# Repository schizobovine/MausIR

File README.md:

# MausIR
Making some toys for my cats.

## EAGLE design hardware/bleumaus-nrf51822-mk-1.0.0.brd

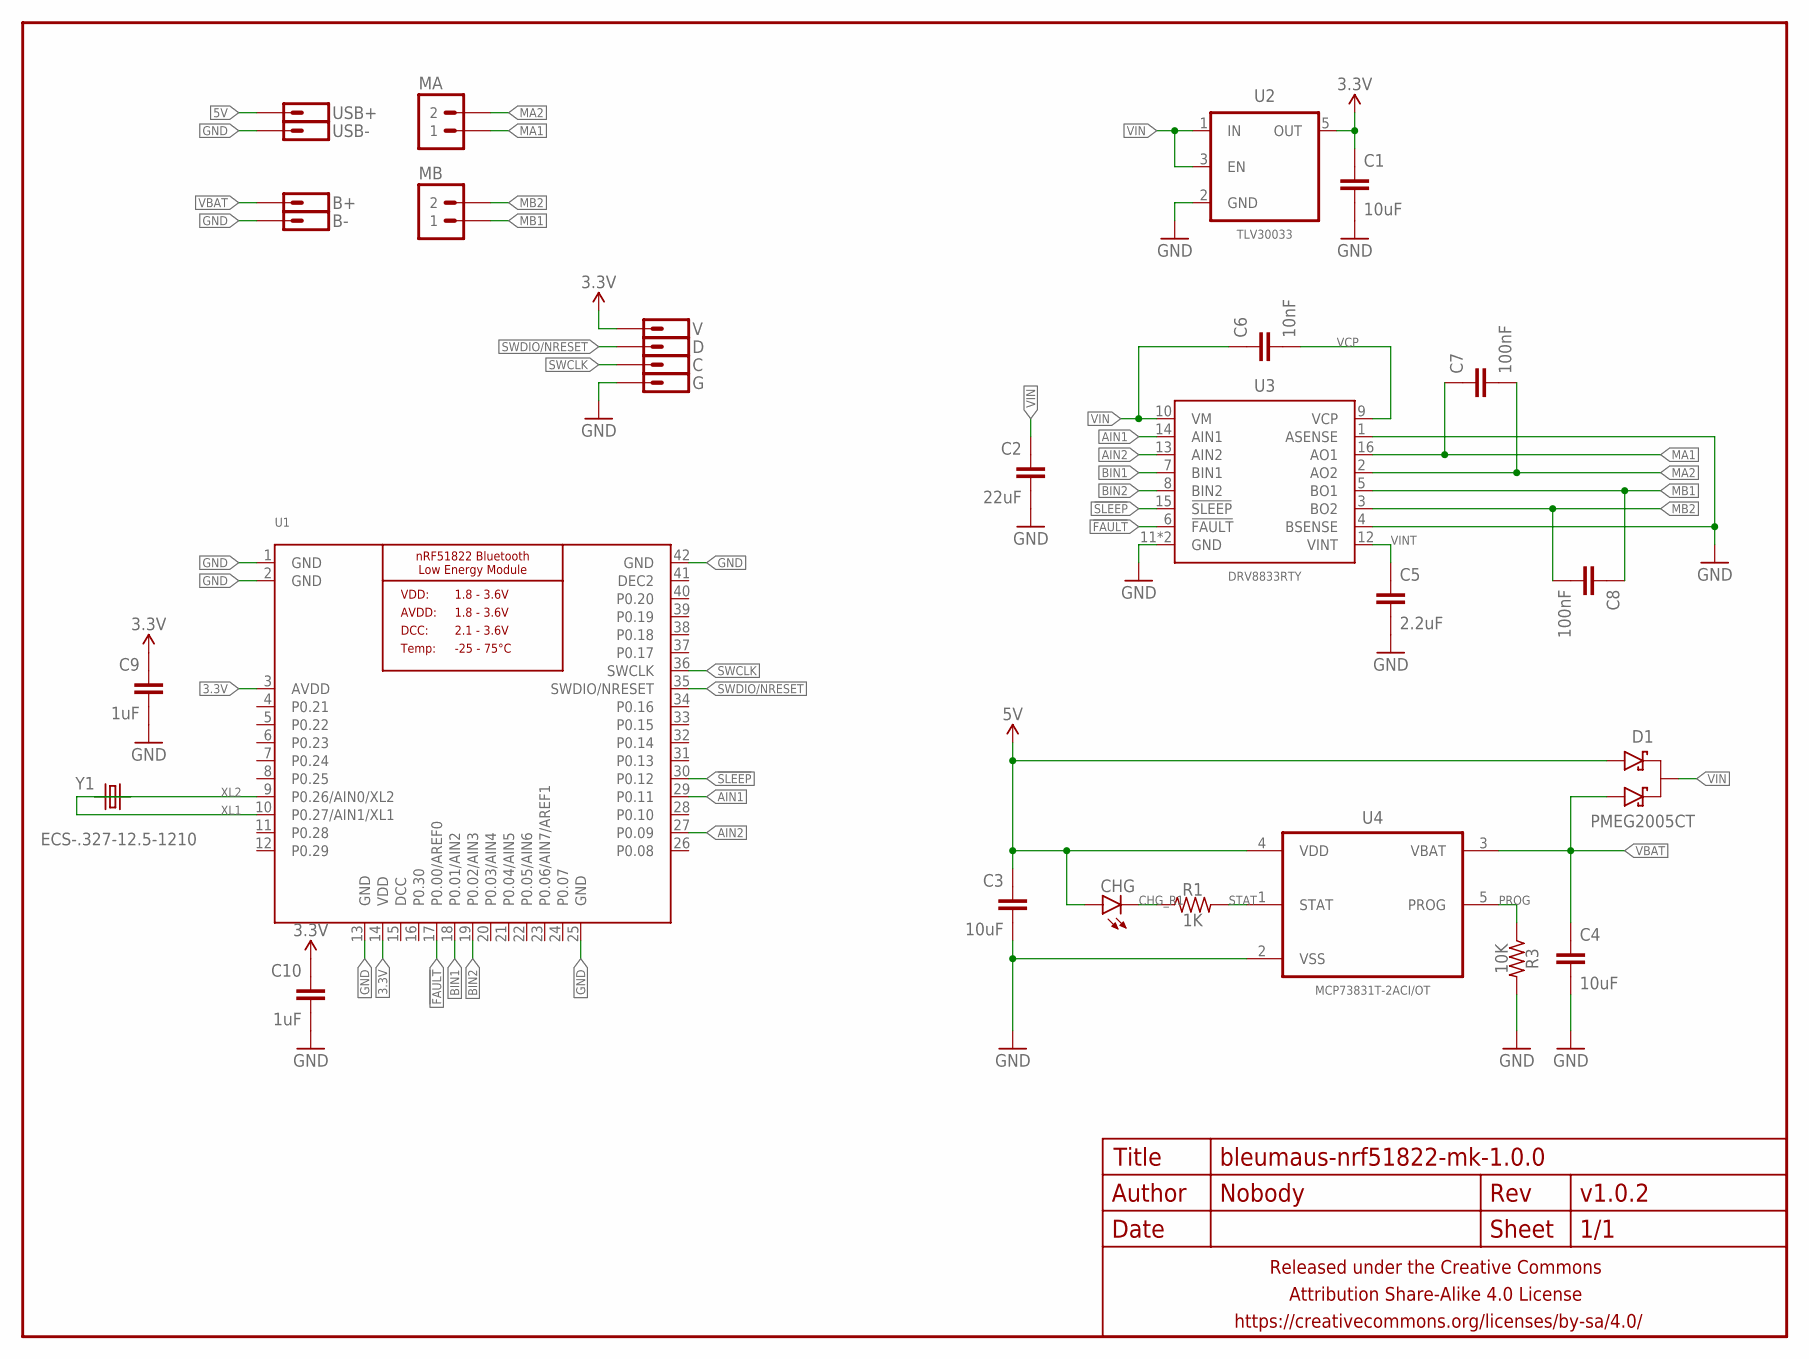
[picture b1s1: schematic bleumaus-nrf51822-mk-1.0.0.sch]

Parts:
B+: M01SMD-1DIA; 1X01-SMD-1MM-DIA
B-: M01SMD-1DIA; 1X01-SMD-1MM-DIA
C: M01SMD-1DIA; 1X01-SMD-1MM-DIA
C1, C3, C4: 10uF; C0402
C2: 22uF; C1206
C5: 2.2uF; C0402
C6: 10nF; C0402
C7, C8: 100nF; C0402
C9, C10: 1uF; C0402
CHG: LED0603-TIGHT; LED-0603-TIGHT
D: M01SMD-1DIA; 1X01-SMD-1MM-DIA
D1: PMEG2005CT; SOT23
FRAME1: FRAME-LETTERNO_PACKAGE; DUMMY
G: M01SMD-1DIA; 1X01-SMD-1MM-DIA
MA: M02PTH-2MM; 1X02-2MM-PTH
MB: M02PTH-2MM; 1X02-2MM-PTH
R1: 1K; R0402
R3: 10K; R0402
U1: NRF51822_MODULE_MDBT40; BLE_MODULE_RAYTAC_MDBT40
U2: TLV30033; SC70-TIGHTER
U3: DRV8833RTY; PWQFN-16
U4: MCP73831T-2ACI/OT; SOT95P280X145-5N
USB+: M01SMD-1DIA; 1X01-SMD-1MM-DIA
USB-: M01SMD-1DIA; 1X01-SMD-1MM-DIA
V: M01SMD-1DIA; 1X01-SMD-1MM-DIA
Y1: ECS-.327-12.5-1210; CRYSTAL-1X1.2MM

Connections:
3.3V: C1.1, C9.1, C10.1, U1.3 (AVDD), U1.14 (VDD), U2.5 (OUT), V.P$1
5V: C3.1, CHG.A, D1.1 (A1), U4.4 (VDD), USB+.P$1
!FAULT: U1.17 (P0.00/AREF0), U3.6 (!FAULT)
!SLEEP: U1.30 (P0.12), U3.15 (!SLEEP)
AIN1: U1.29 (P0.11), U3.14 (AIN1)
AIN2: U1.27 (P0.09), U3.13 (AIN2)
BIN1: U1.18 (P0.01/AIN2), U3.7 (BIN1)
BIN2: U1.19 (P0.02/AIN3), U3.8 (BIN2)
CHG_R1: CHG.C, R1.1
DCC: U1.15 (DCC)
DEC2: U1.41 (DEC2)
GND: B-.P$1, C1.2, C2.2, C3.2, C4.2, C5.2, C9.2, C10.2, G.P$1, R3.2, U1.1 (GND), U1.2 (GND), U1.13 (GND), U1.25 (GND), U1.42 (GND), U2.2 (GND), U3.1 (ASENSE), U3.4 (BSENSE), U3.11 (GND), U3.17 (GND), U4.2 (VSS), USB-.P$1
MA1: C7.1, MA.P$1 (1), U3.16 (AO1)
MA2: C7.2, MA.P$2 (2), U3.2 (AO2)
MB1: C8.1, MB.P$1 (1), U3.5 (BO1)
MB2: C8.2, MB.P$2 (2), U3.3 (BO2)
PROG: R3.1, U4.5 (PROG)
STAT: R1.2, U4.1 (STAT)
SWCLK: C.P$1, U1.36 (SWCLK)
SWDIO/NRESET: D.P$1, U1.35 (SWDIO/NRESET)
VBAT: B+.P$1, C4.1, D1.2 (A2), U4.3 (VBAT)
VCP: C6.2, U3.9 (VCP)
VIN: C2.1, C6.1, D1.3 (K), U2.1 (IN), U2.3 (EN), U3.10 (VM)
VINT: C5.1, U3.12 (VINT)
XL1: U1.10 (P0.27/AIN1/XL1), Y1.1
XL2: U1.9 (P0.26/AIN0/XL2), Y1.2

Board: 2 copper layers, 30 parts (19 on the bottom side), 24 nets, no tracks yet.

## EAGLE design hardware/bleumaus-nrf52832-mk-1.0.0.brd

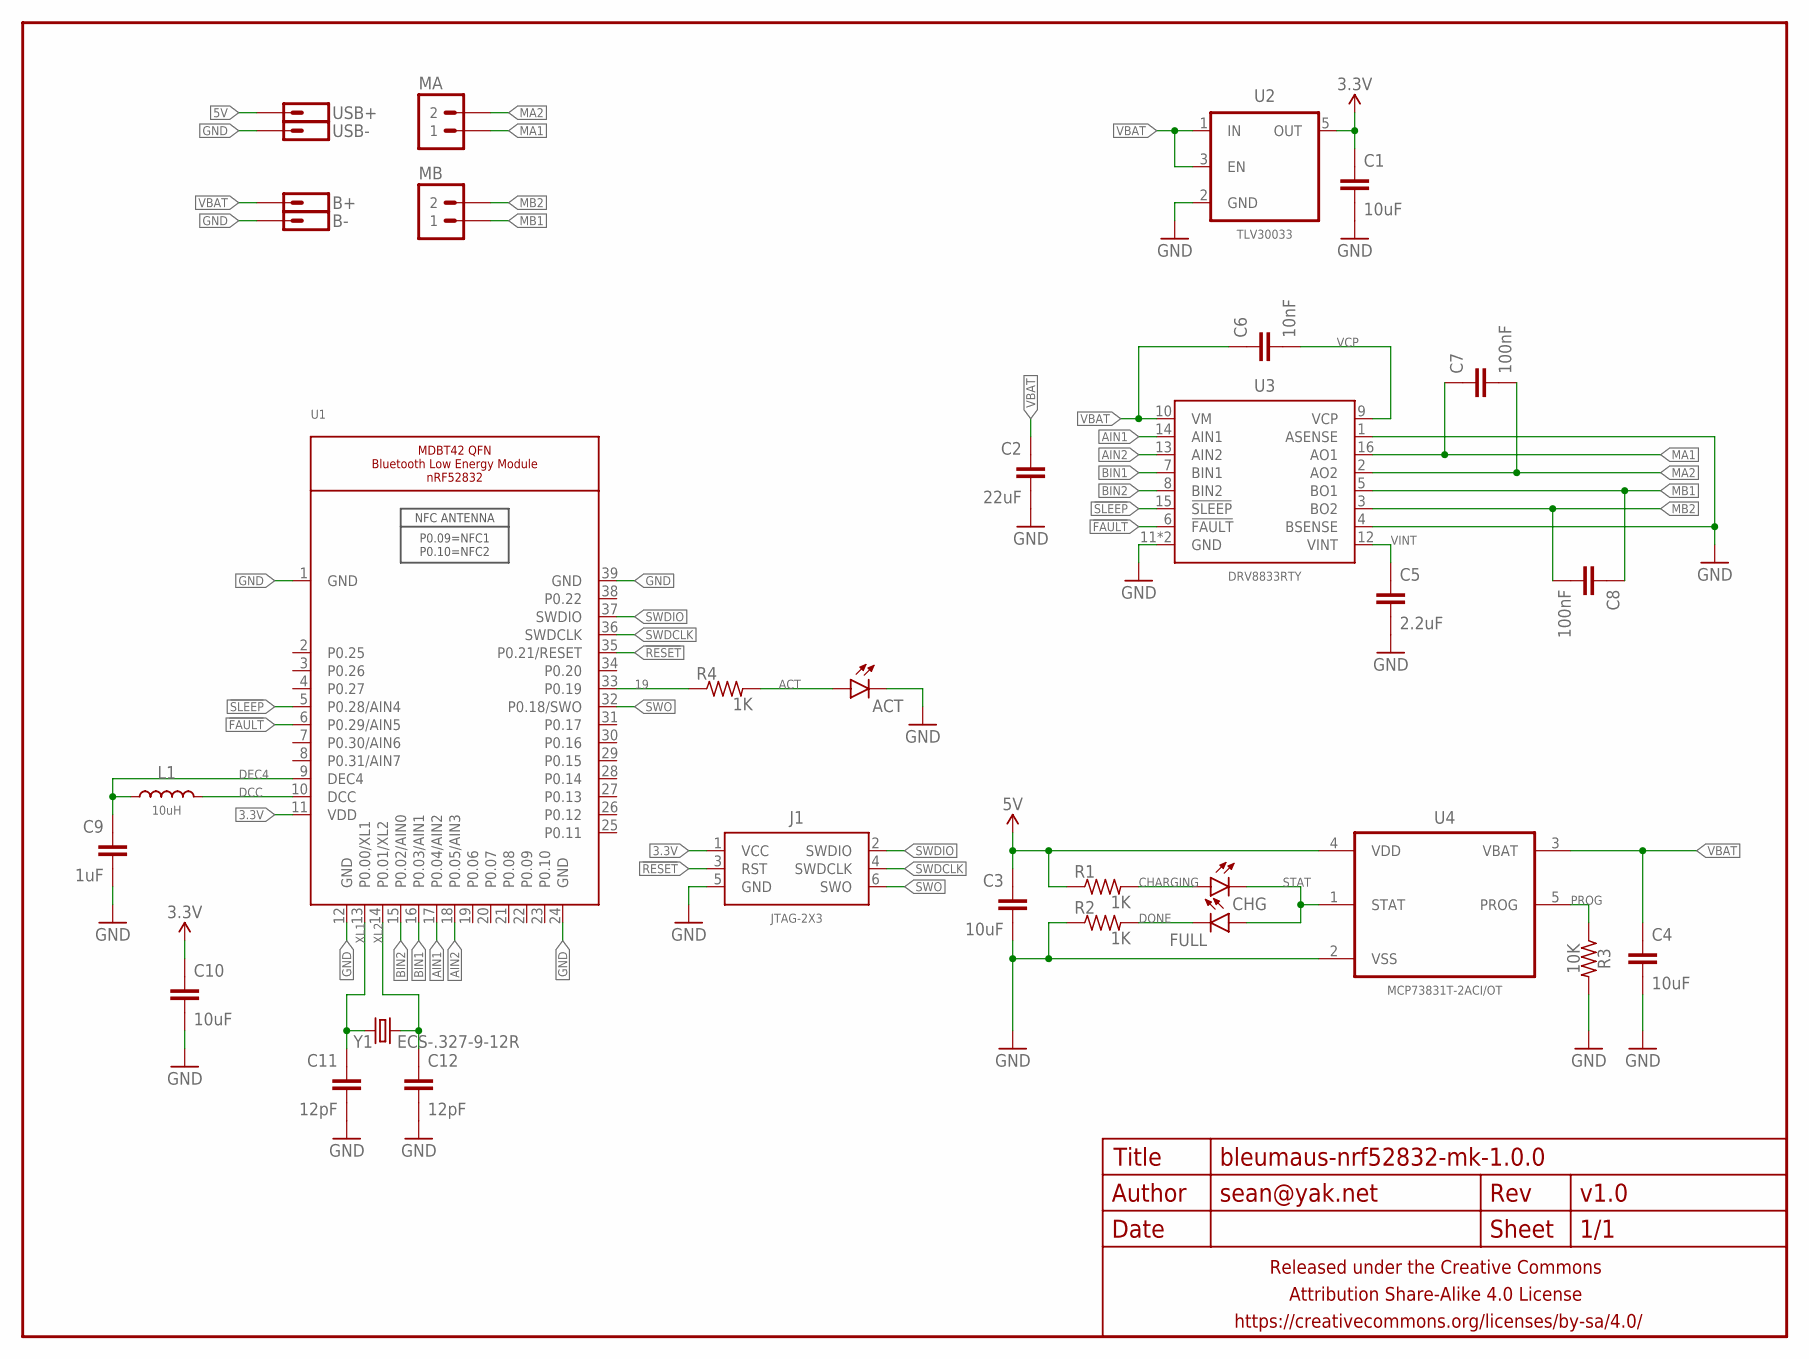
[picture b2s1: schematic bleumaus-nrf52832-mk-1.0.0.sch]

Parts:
ACT: LED0603-TIGHT; LED-0603-TIGHT
B+: M01SMD-1DIA; 1X01-SMD-1MM-DIA
B-: M01SMD-1DIA; 1X01-SMD-1MM-DIA
C1, C3, C4: 10uF; C0402
C2: 22uF; C1206
C5: 2.2uF; C0402
C6: 10nF; C0402
C7, C8: 100nF; C0402
C9: 1uF; C0402
C10: 10uF; C0603-TIGHTER
C11, C12: 12pF; C0402
CHG: LED0603-TIGHT; LED-0603-TIGHT
FRAME1: FRAME-LETTERNO_PACKAGE; DUMMY
FULL: LED0603-TIGHT; LED-0603-TIGHT
J1: JTAG-2X3; 2X3-1.27MM-SMD
L1: 10uH; 0603
MA: M02PTH-2MM; 1X02-2MM-PTH
MB: M02PTH-2MM; 1X02-2MM-PTH
R1, R2, R4: 1K; R0402
R3: 10K; R0402
U1: NRF52832_MODULE_MDBT42_NO2324; BLE_MODULE_RAYTAC_MDBT42_NO2324
U2: TLV30033; SC70-TIGHTER
U3: DRV8833RTY; PWQFN-16
U4: MCP73831T-2ACI/OT; SOT95P280X145-5N
USB+: M01SMD-1DIA; 1X01-SMD-1MM-DIA
USB-: M01SMD-1DIA; 1X01-SMD-1MM-DIA
Y1: ECS-.327-9-12R; CRYSTAL-2X1.2MM

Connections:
3.3V: C1.1, C10.1, J1.1 (VCC), U1.11 (VDD), U2.5 (OUT)
5V: C3.1, R1.1, U4.4 (VDD), USB+.P$1
19: R4.1, U1.33 (P0.19)
!FAULT: U1.6 (P0.29/AIN5), U3.6 (!FAULT)
!RESET: J1.3 (RST), U1.35 (P0.21/RESET)
!SLEEP: U1.5 (P0.28/AIN4), U3.15 (!SLEEP)
ACT: ACT.A, R4.2
AIN1: U1.17 (P0.04/AIN2), U3.14 (AIN1)
AIN2: U1.18 (P0.05/AIN3), U3.13 (AIN2)
BIN1: U1.16 (P0.03/AIN1), U3.7 (BIN1)
BIN2: U1.15 (P0.02/AIN0), U3.8 (BIN2)
CHARGING: CHG.A, R1.2
DCC: L1.2, U1.10 (DCC)
DEC4: C9.1, L1.1, U1.9 (DEC4)
DONE: FULL.C, R2.2
GND: ACT.C, B-.P$1, C1.2, C2.2, C3.2, C4.2, C5.2, C9.2, C10.2, C11.2, C12.2, J1.5 (GND), R2.1, R3.2, U1.1 (GND), U1.12 (GND), U1.24 (GND), U1.39 (GND), U2.2 (GND), U3.1 (ASENSE), U3.4 (BSENSE), U3.11 (GND), U3.17 (GND), U4.2 (VSS), USB-.P$1
MA1: C7.1, MA.P$1 (1), U3.16 (AO1)
MA2: C7.2, MA.P$2 (2), U3.2 (AO2)
MB1: C8.1, MB.P$1 (1), U3.5 (BO1)
MB2: C8.2, MB.P$2 (2), U3.3 (BO2)
PROG: R3.1, U4.5 (PROG)
STAT: CHG.C, FULL.A, U4.1 (STAT)
SWDCLK: J1.4 (SWDCLK), U1.36 (SWDCLK)
SWDIO: J1.2 (SWDIO), U1.37 (SWDIO)
SWO: J1.6 (SWO), U1.32 (P0.18/SWO)
VBAT: B+.P$1, C2.1, C4.1, C6.1, U2.1 (IN), U2.3 (EN), U3.10 (VM), U4.3 (VBAT)
VCP: C6.2, U3.9 (VCP)
VINT: C5.1, U3.12 (VINT)
XL1: C11.1, U1.13 (P0.00/XL1), Y1.1
XL2: C12.1, U1.14 (P0.01/XL2), Y1.2

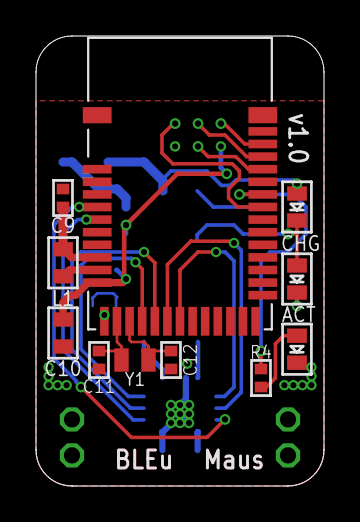
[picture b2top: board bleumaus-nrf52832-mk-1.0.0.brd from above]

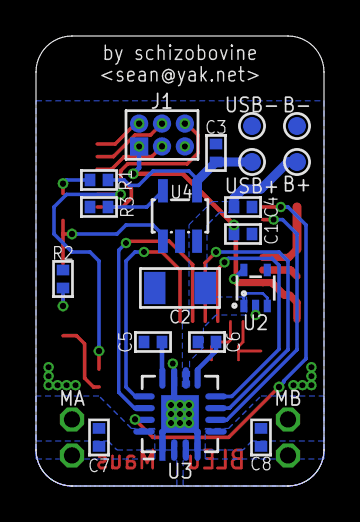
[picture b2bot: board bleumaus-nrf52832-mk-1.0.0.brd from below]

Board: 2 copper layers, 16.0 x 25.0 mm, 33 parts (21 on the bottom side), 30 nets.

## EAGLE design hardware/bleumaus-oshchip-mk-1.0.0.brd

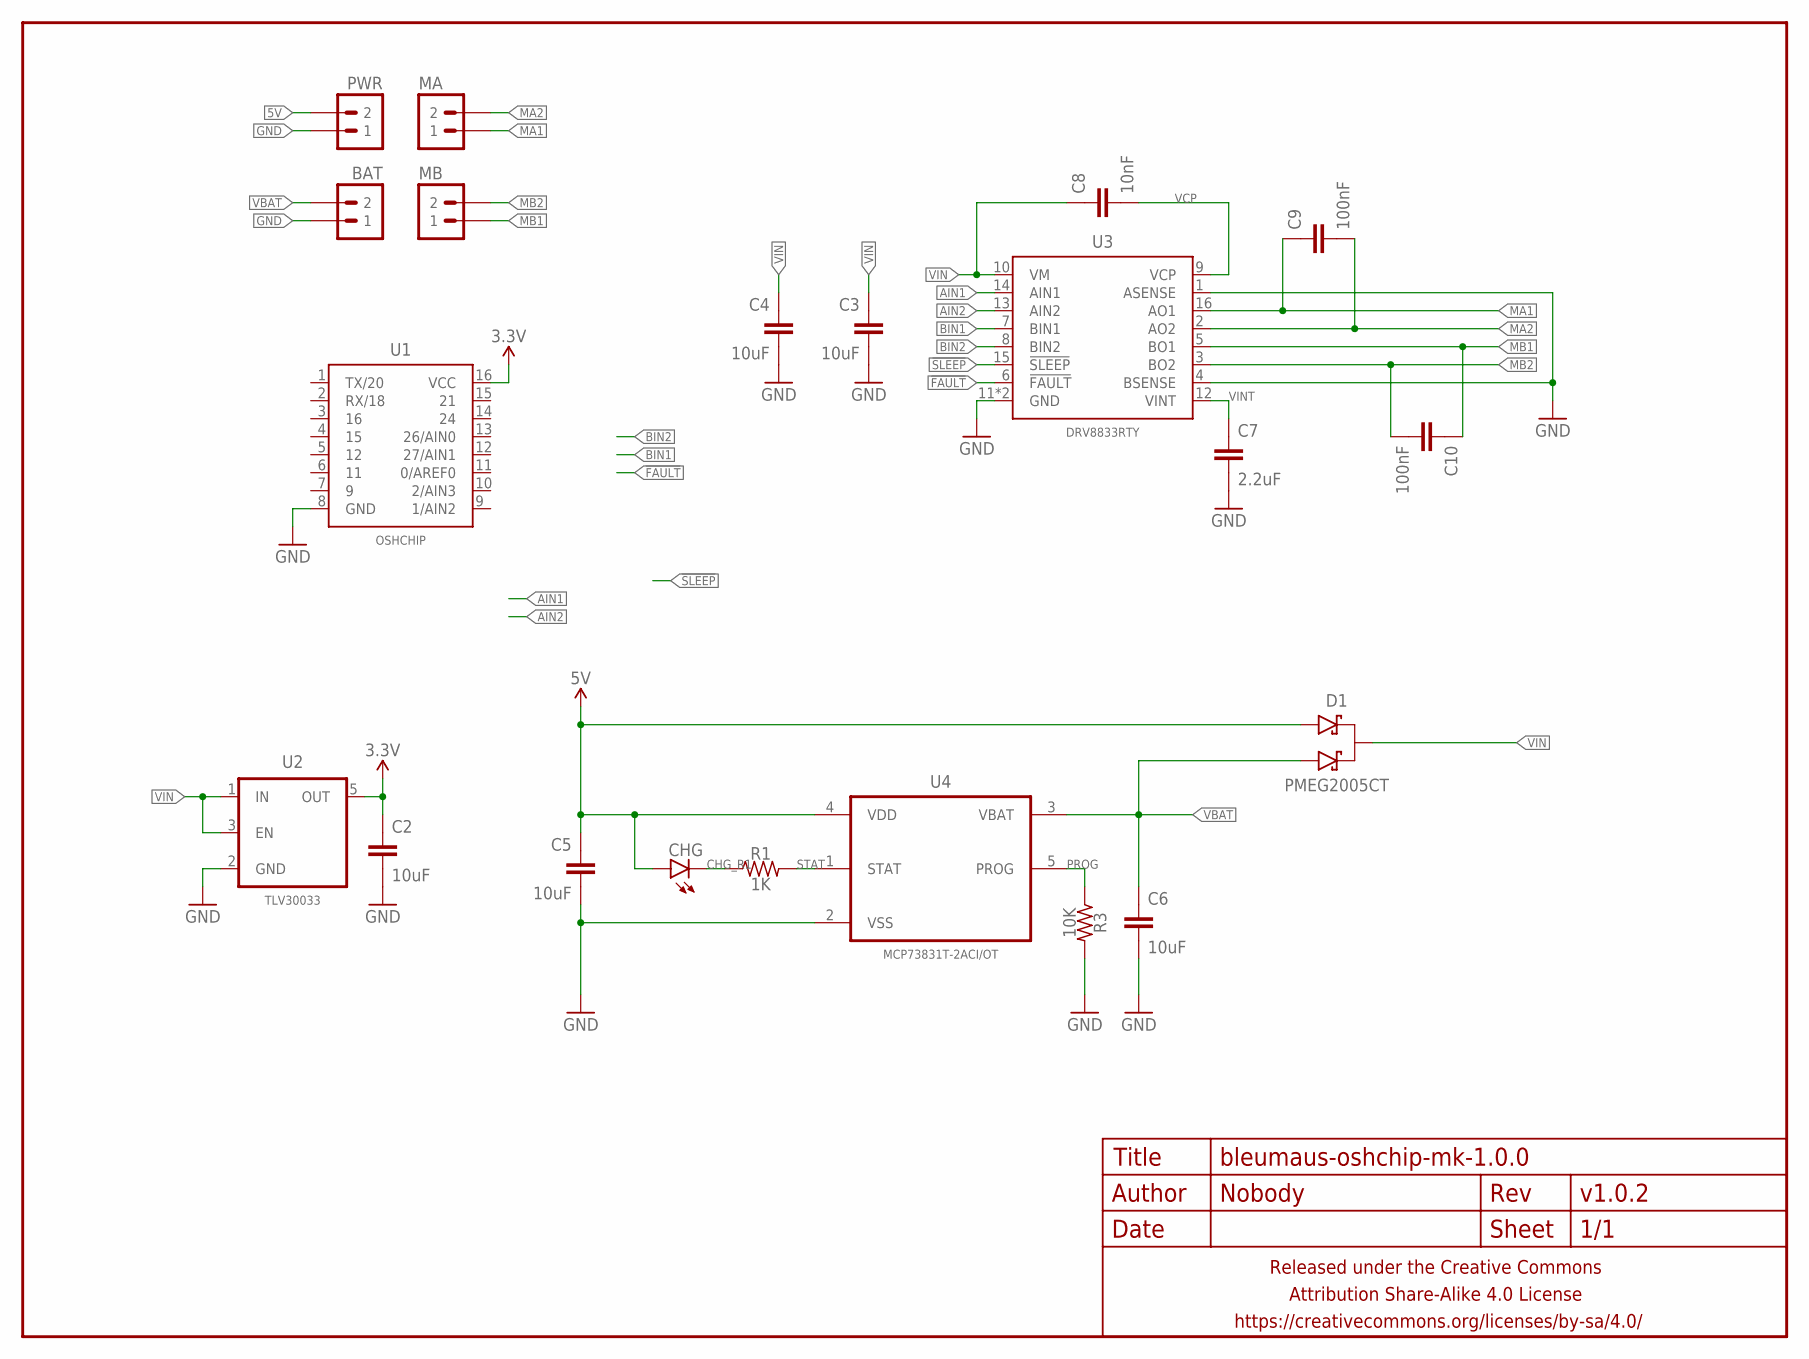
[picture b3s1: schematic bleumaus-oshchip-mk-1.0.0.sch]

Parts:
BAT: M02PTH-2MM; 1X02-2MM-PTH
C2, C5, C6: 10uF; C0402
C3, C4: 10uF; C1206
C7: 2.2uF; C0402
C8: 10nF; C0402
C9, C10: 100nF; C0402
CHG: LED0603-TIGHT; LED-0603-TIGHT
D1: PMEG2005CT; SOT23
FRAME1: FRAME-LETTERNO_PACKAGE; DUMMY
MA: M02PTH-2MM; 1X02-2MM-PTH
MB: M02PTH-2MM; 1X02-2MM-PTH
PWR: M02PTH-2MM; 1X02-2MM-PTH
R1: 1K; R0402
R3: 10K; R0402
U1: OSHCHIP; DIL16
U2: TLV30033; SC70-TIGHTER
U3: DRV8833RTY; PWQFN-16
U4: MCP73831T-2ACI/OT; SOT95P280X145-5N

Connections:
3.3V: C2.1, U1.16 (VCC), U2.5 (OUT)
5V: C5.1, CHG.A, D1.1 (A1), PWR.P$2 (2), U4.4 (VDD)
!FAULT: U3.6 (!FAULT)
!SLEEP: U3.15 (!SLEEP)
AIN1: U3.14 (AIN1)
AIN2: U3.13 (AIN2)
BIN1: U3.7 (BIN1)
BIN2: U3.8 (BIN2)
CHG_R1: CHG.C, R1.1
GND: BAT.P$1 (1), C2.2, C3.2, C4.2, C5.2, C6.2, C7.2, PWR.P$1 (1), R3.2, U1.8 (GND), U2.2 (GND), U3.1 (ASENSE), U3.4 (BSENSE), U3.11 (GND), U3.17 (GND), U4.2 (VSS)
MA1: C9.1, MA.P$1 (1), U3.16 (AO1)
MA2: C9.2, MA.P$2 (2), U3.2 (AO2)
MB1: C10.1, MB.P$1 (1), U3.5 (BO1)
MB2: C10.2, MB.P$2 (2), U3.3 (BO2)
PROG: R3.1, U4.5 (PROG)
STAT: R1.2, U4.1 (STAT)
VBAT: BAT.P$2 (2), C6.1, D1.2 (A2), U4.3 (VBAT)
VCP: C8.2, U3.9 (VCP)
VIN: C3.1, C4.1, C8.1, D1.3 (K), U2.1 (IN), U2.3 (EN), U3.10 (VM)
VINT: C7.1, U3.12 (VINT)

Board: 2 copper layers, 22 parts (2 on the bottom side), 14 nets, no tracks yet.

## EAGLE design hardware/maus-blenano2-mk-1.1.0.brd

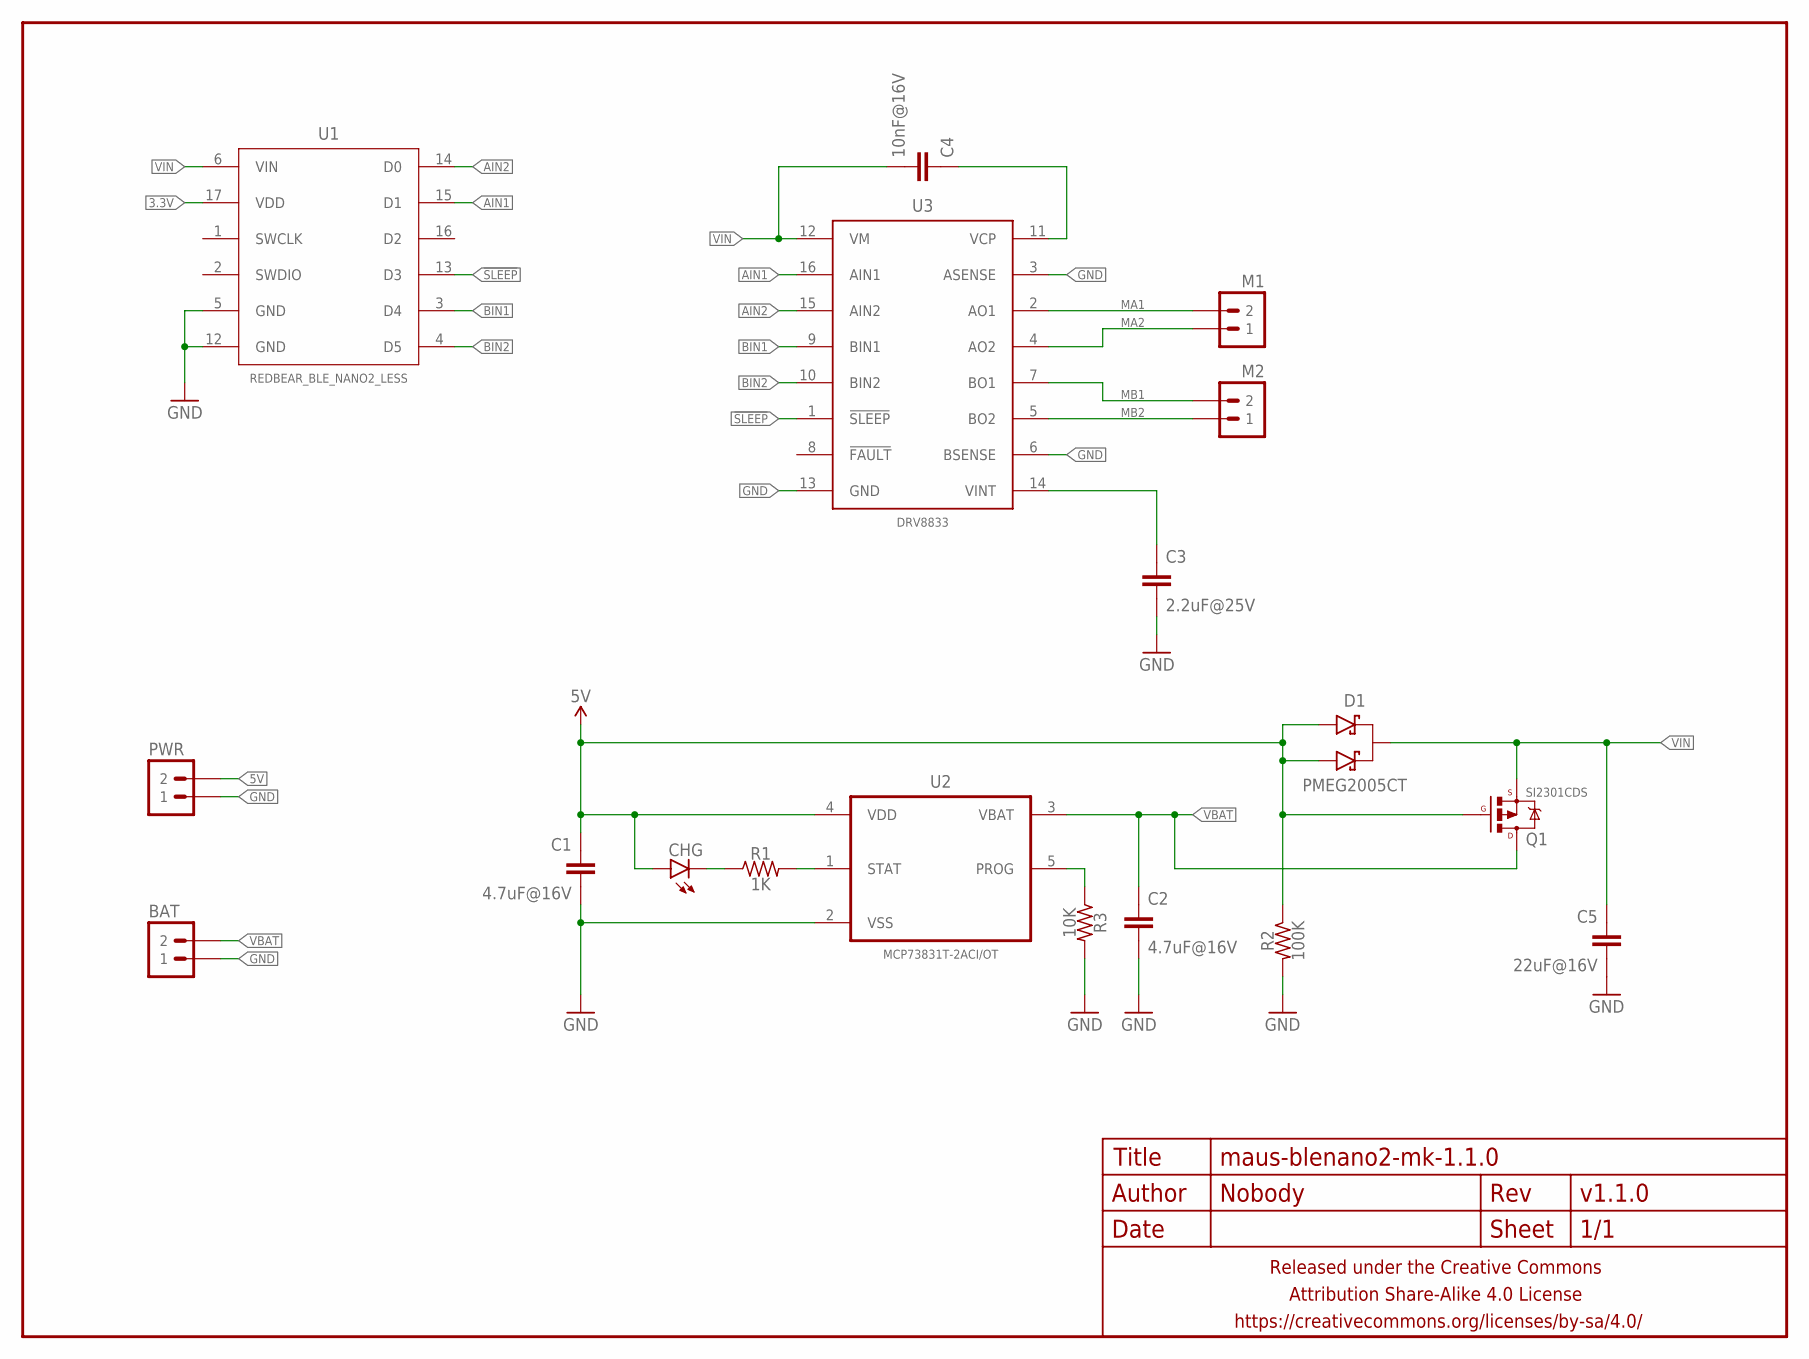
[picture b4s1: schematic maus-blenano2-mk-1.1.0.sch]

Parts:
BAT: M02PTH-2MM; 1X02-2MM-PTH
C1, C2: 4.7uF@16V; C0603-TIGHTER
C3: 2.2uF@25V; C0603
C4: 10nF@16V; C0402
C5: 22uF@16V; C1206
CHG: LED0603-TIGHT; LED-0603-TIGHT
D1: PMEG2005CT; SOT23
FRAME1: FRAME-LETTERNO_PACKAGE; DUMMY
M1, M2: M02PTH-2MM; 1X02-2MM-PTH
PWR: M02PTH-2MM; 1X02-2MM-PTH
Q1: SI2301CDS; SOT23
R1: 1K; R0603-TIGHTER
R2: 100K; R0603-TIGHTER
R3: 10K; R0603-TIGHTER
U1: REDBEAR_BLE_NANO2_LESS
U2: MCP73831T-2ACI/OT; SOT95P280X145-5N
U3: DRV8833; TSSOP16

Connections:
3.3V: U1.17 (VDD)
5V: C1.1, CHG.A, D1.1 (A1), D1.2 (A2), PWR.P$2 (2), Q1.1 (G), R2.1, U2.4 (VDD)
!SLEEP: U1.13 (D3), U3.1 (!SLEEP)
AIN1: U1.15 (D1), U3.16 (AIN1)
AIN2: U1.14 (D0), U3.15 (AIN2)
BIN1: U1.3 (D4), U3.9 (BIN1)
BIN2: U1.4 (D5), U3.10 (BIN2)
GND: BAT.P$1 (1), C1.2, C2.2, C3.2, C5.2, PWR.P$1 (1), R2.2, R3.2, U1.5 (GND), U1.12 (GND), U2.2 (VSS), U3.3 (ASENSE), U3.6 (BSENSE), U3.13 (GND)
MA1: M1.P$2 (2), U3.2 (AO1)
MA2: M1.P$1 (1), U3.4 (AO2)
MB1: M2.P$2 (2), U3.7 (BO1)
MB2: M2.P$1 (1), U3.5 (BO2)
unnamed: R1.2, U2.1 (STAT)
unnamed: CHG.C, R1.1
unnamed: C3.1, U3.14 (VINT)
unnamed: C4.1, U3.11 (VCP)
unnamed: R3.1, U2.5 (PROG)
VBAT: BAT.P$2 (2), C2.1, Q1.3 (D), U2.3 (VBAT)
VIN: C4.2, C5.1, D1.3 (K), Q1.2 (S), U1.6 (VIN), U3.12 (VM)

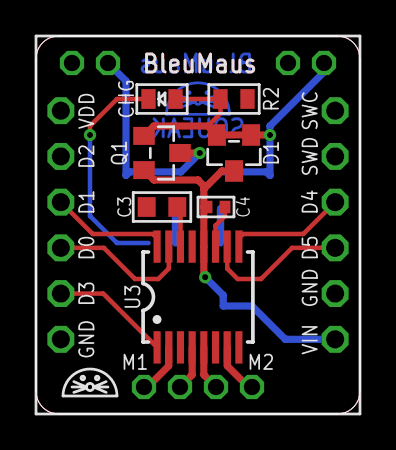
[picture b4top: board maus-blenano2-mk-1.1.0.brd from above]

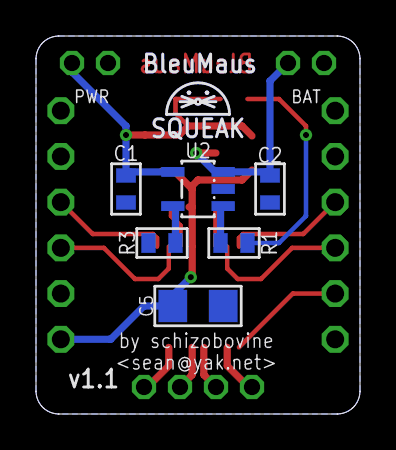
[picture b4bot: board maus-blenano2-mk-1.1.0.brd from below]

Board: 2 copper layers, 18.0 x 21.0 mm, 19 parts (8 on the bottom side), 18 nets.

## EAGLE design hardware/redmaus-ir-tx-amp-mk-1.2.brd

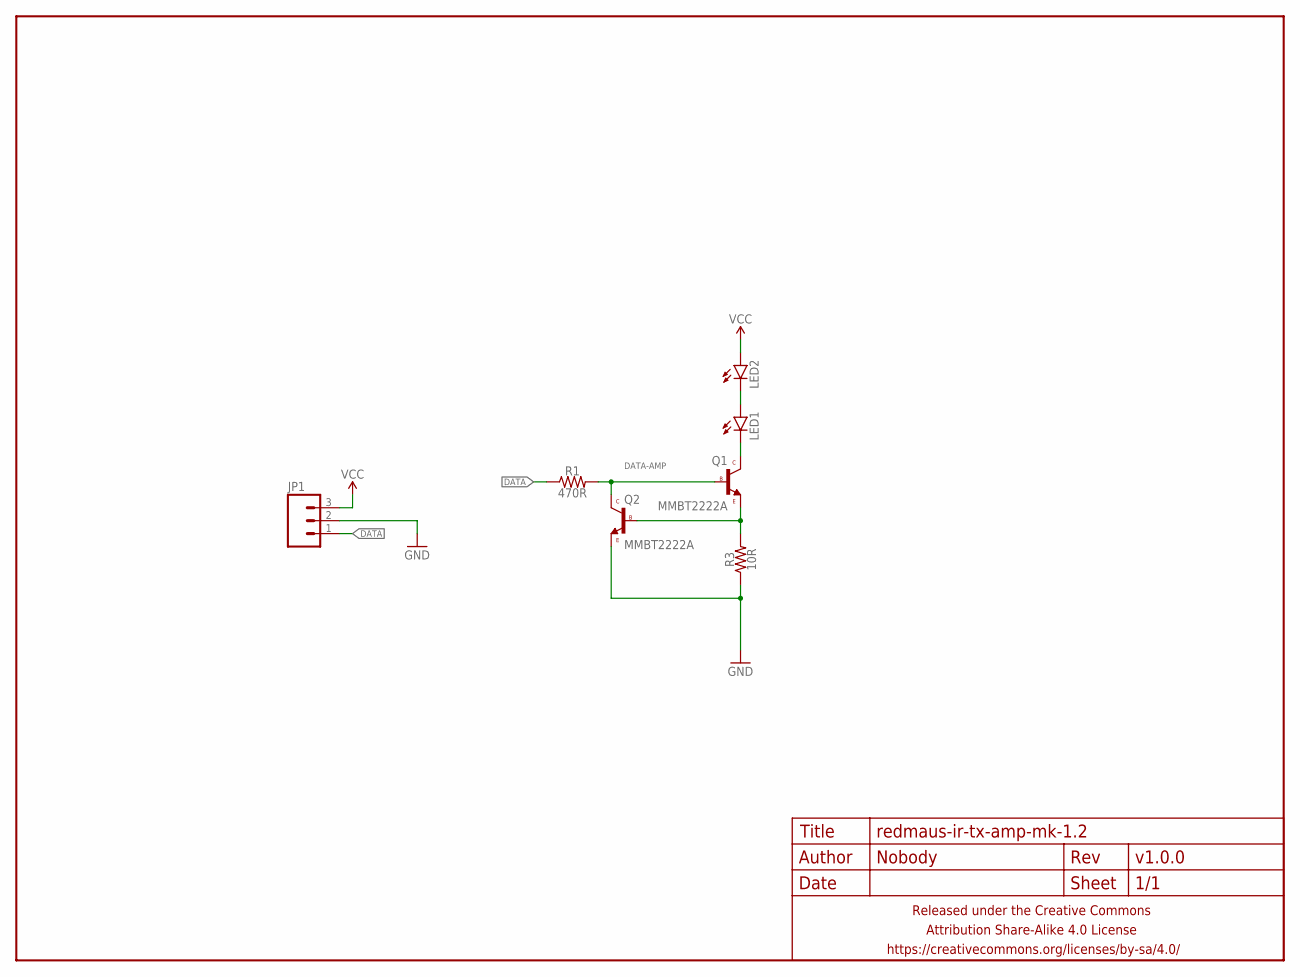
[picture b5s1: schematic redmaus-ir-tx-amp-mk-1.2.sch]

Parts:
FRAME1: FRAME-LETTERNO_PACKAGE; DUMMY
JP1: M03PTH-CENTERED; 1X03-CENTERED
LED1, LED2: LED5MM_SHORTPADS
Q1, Q2: MMBT2222A; SOT23
R1: 470R; R0603-TIGHTER
R3: 10R; R0603-TIGHTER

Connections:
DATA: JP1.1, R1.1
DATA-AMP: Q1.1 (B), Q2.3 (C), R1.2
GND: JP1.2, Q2.2 (E), R3.1
unnamed: LED1.A, LED2.K (C)
unnamed: LED1.K (C), Q1.3 (C)
unnamed: Q1.2 (E), Q2.1 (B), R3.2
VCC: JP1.3, LED2.A

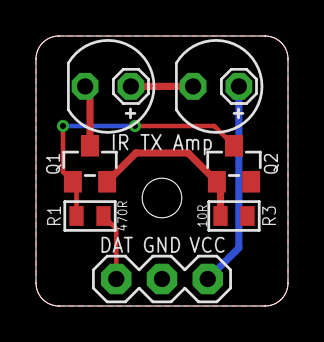
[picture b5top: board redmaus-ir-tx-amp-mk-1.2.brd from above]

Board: 2 copper layers, 14.0 x 15.0 mm, 8 parts (0 on the bottom side), 7 nets.

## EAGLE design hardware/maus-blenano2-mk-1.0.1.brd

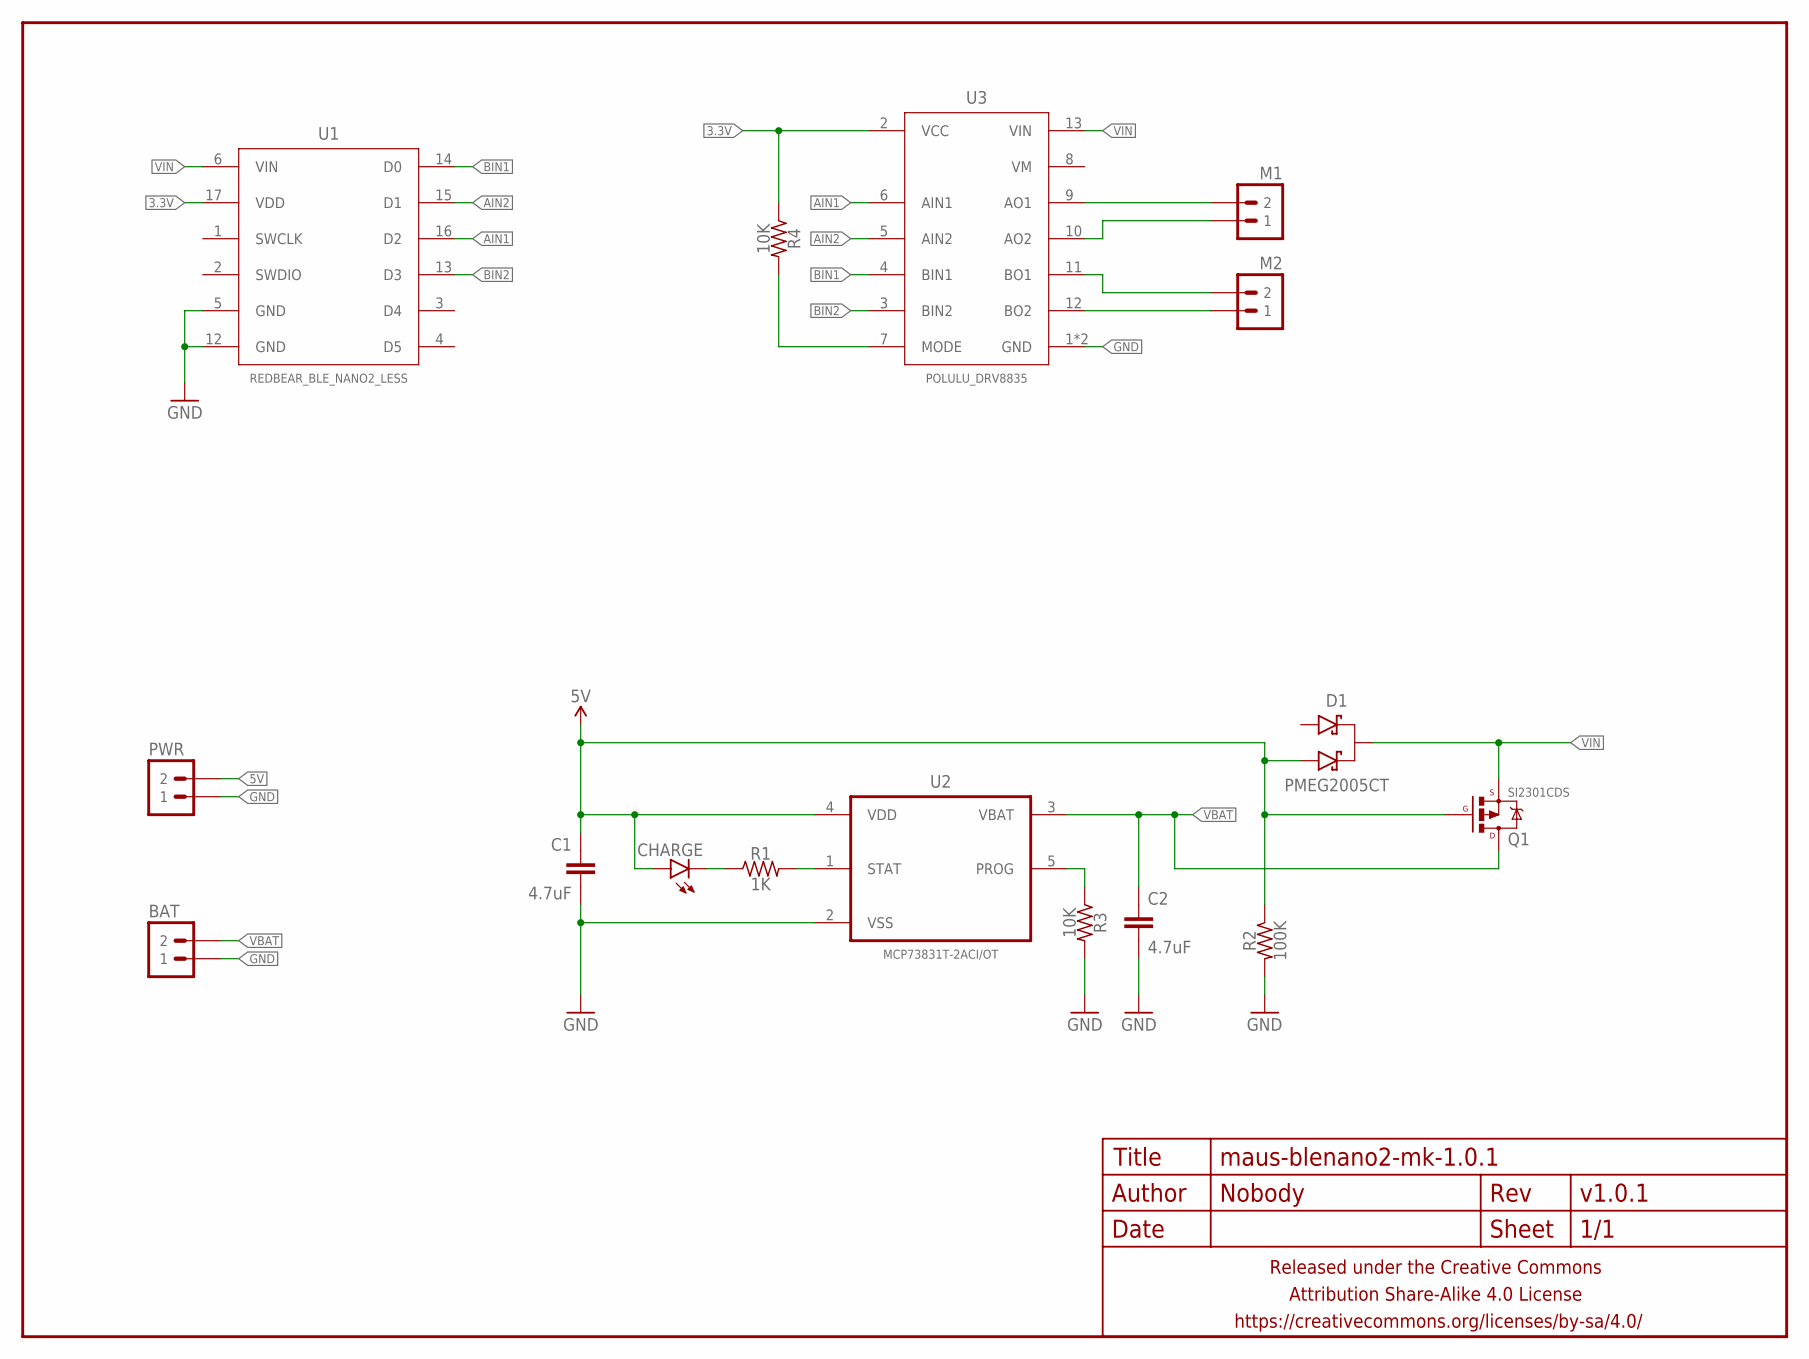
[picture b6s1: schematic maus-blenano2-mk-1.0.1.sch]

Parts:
BAT: M02JST-SH-RA; JST-2-SH-RA
C1, C2: 4.7uF; C0603-TIGHTER
CHARGE: LED0603-TIGHT; LED-0603-TIGHT
D1: PMEG2005CT; SOT23
FRAME1: FRAME-LETTERNO_PACKAGE; DUMMY
M1, M2: M02PTH-2MM; 1X02-2MM-PTH
PWR: M02JST-SH-RA; JST-2-SH-RA
Q1: SI2301CDS; SOT23
R1: 1K; R0603-TIGHTER
R2: 100K; R0603-TIGHTER
R3, R4: 10K; R0603-TIGHTER
U1: REDBEAR_BLE_NANO2_LESS
U2: MCP73831T-2ACI/OT; SOT95P280X145-5N
U3: POLULU_DRV8835

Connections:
3.3V: R4.1, U1.17 (VDD), U3.2 (VCC)
5V: C1.1, CHARGE.A, D1.2 (A2), PWR.2, Q1.1 (G), R2.1, U2.4 (VDD)
AIN1: U1.16 (D2), U3.6 (AIN1)
AIN2: U1.15 (D1), U3.5 (AIN2)
BIN1: U1.14 (D0), U3.4 (BIN1)
BIN2: U1.13 (D3), U3.3 (BIN2)
GND: BAT.1, C1.2, C2.2, PWR.1, R2.2, R3.2, U1.5 (GND), U1.12 (GND), U2.2 (VSS), U3.1 (GND), U3.14 (GND)
unnamed: R1.2, U2.1 (STAT)
unnamed: CHARGE.C, R1.1
unnamed: R4.2, U3.7 (MODE)
unnamed: M1.P$2 (2), U3.9 (AO1)
unnamed: M1.P$1 (1), U3.10 (AO2)
unnamed: M2.P$2 (2), U3.11 (BO1)
unnamed: M2.P$1 (1), U3.12 (BO2)
unnamed: R3.1, U2.5 (PROG)
VBAT: BAT.2, C2.1, Q1.3 (D), U2.3 (VBAT)
VIN: D1.3 (K), Q1.2 (S), U1.6 (VIN), U3.13 (VIN)

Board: 2 copper layers, 17 parts (10 on the bottom side), 17 nets, no tracks yet.

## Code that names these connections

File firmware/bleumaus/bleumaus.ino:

//
// bleumaus.ino
//
// Modified mouse robot toy for my cats. Now with Bluetooth!
//
// Author:  Sean Caulfield <sean@yak.net>
// License: GPLv3.0
//

#include <Arduino.h>
#include <bluefruit.h>
#include <Adafruit_LittleFS.h>
#include <InternalFileSystem.h>
#include <Chrono.h>

// Debugging macros/settings

#define DEBUG_SERIAL      (0)

#if (DEBUG_SERIAL)
#define DPRINT(...) Serial.print(__VA_ARGS__)
#define DPRINTLN(...) Serial.println(__VA_ARGS__)
#else
#define DPRINT(...)
#define DPRINTLN(...)
#endif

#define CMD_DURATION      (500) // in ms, how long should a movement command
                                // "run" before returning to coasting?

// Is channel A the:
//  LEFT  (true)  -OR-  RIGHT (false)
// wheel?
#define IS_A_LEFT         (false)

// Is "forward" actually "reverse"?
#define REVERSED          (true)

#define BLE_UART_NAME     ("BleuMaus")

#define PIN_AIN1          (4)
#define PIN_AIN2          (5)
#define PIN_BIN1          (3)
#define PIN_BIN2          (2)
#define PIN_SLEEP         (28)
#define PIN_FAULT         (29)

// Bluetooth LE service objects
BLEDfu  ble_dfu;  // Over-the-air (OTA) Device Firmware Update (DFU)
BLEDis  ble_dis;  // Device Information Service
BLEUart ble_uart; // UART over BLE
BLEBas  ble_bas;  // BLE battery service

// Command buffer
//byte cmd[CMD_BUFF_SZ];

// Command duration timer
Chrono cmd_timer;

// Motor speed variables
int16_t curr_motor_l = 0;
int16_t curr_motor_r = 0;

/**
 * Dispatch movement commands.
 */
void dispatch_movement() {
    if (curr_motor_l > 0 && curr_motor_r > 0) { //forward
        digitalWrite(PIN_SLEEP, HIGH);
        digitalWrite(PIN_AIN1, (REVERSED) ? LOW : HIGH);
        digitalWrite(PIN_BIN1, (REVERSED) ? LOW : HIGH);
        analogWrite(PIN_AIN2, abs((IS_A_LEFT) ? curr_motor_l : curr_motor_r));
        analogWrite(PIN_BIN2, abs((IS_A_LEFT) ? curr_motor_r : curr_motor_l));
    } else if (curr_motor_l > 0 && curr_motor_r < 0) { // right
        digitalWrite(PIN_SLEEP, HIGH);
        digitalWrite(PIN_AIN1, (IS_A_LEFT) ? HIGH : LOW);
        digitalWrite(PIN_BIN1, (IS_A_LEFT) ? LOW : HIGH);
        analogWrite(PIN_AIN2, abs((IS_A_LEFT) ? curr_motor_l : curr_motor_r));
        analogWrite(PIN_BIN2, abs((IS_A_LEFT) ? curr_motor_r : curr_motor_l));
    } else if (curr_motor_l < 0 && curr_motor_r > 0) { // left
        digitalWrite(PIN_SLEEP, HIGH);
        digitalWrite(PIN_AIN1, (IS_A_LEFT) ? LOW : HIGH);
        digitalWrite(PIN_BIN1, (IS_A_LEFT) ? HIGH : LOW);
        analogWrite(PIN_AIN2, abs((IS_A_LEFT) ? curr_motor_l : curr_motor_r));
        analogWrite(PIN_BIN2, abs((IS_A_LEFT) ? curr_motor_r : curr_motor_l));
    } else if (curr_motor_l < 0 && curr_motor_r < 0) { // reverse
        digitalWrite(PIN_SLEEP, HIGH);
        digitalWrite(PIN_AIN1, (REVERSED) ? HIGH : LOW);
        digitalWrite(PIN_BIN1, (REVERSED) ? HIGH : LOW);
        analogWrite(PIN_AIN2, abs((IS_A_LEFT) ? curr_motor_l : curr_motor_r));
        analogWrite(PIN_BIN2, abs((IS_A_LEFT) ? curr_motor_r : curr_motor_l));
    } else {
        digitalWrite(PIN_SLEEP, LOW);
        digitalWrite(PIN_AIN1, LOW);
        digitalWrite(PIN_AIN2, LOW);
        digitalWrite(PIN_BIN1, LOW);
        digitalWrite(PIN_BIN2, LOW);
    }
}

/**
 * Callback invoked when we get a BLE connection.
 * @param conn_handle Connection where event happens.
 */
void connect_callback(uint16_t conn_handle) {
  BLEConnection *con = Bluefruit.Connection(conn_handle);

  // Print out name of central that connected to us
  char central_name[32] = { 0 };
  con->getPeerName(central_name, sizeof(central_name));
  DPRINT(F("Connected to "));
  DPRINTLN(central_name);
}

/**
 * Callback invoked when connection is dropped.
 * @param conn_handle Connection where event happens.
 * @param reason BLE_HCI_STATUS_CODE found in ble_hci.h.
 */
void disconnect_callback(uint16_t conn_handle, uint8_t reason) {
  DPRINTLN("Disconnected");
}

void setup() {
    //pinMode(17, OUTPUT);
    //digitalWrite(17, HIGH);

    // Setup serial connection, hopefully this doesn't stall?
#if (DEBUG_SERIAL)
    Serial.begin(115200);
    while (!Serial) {
      delay(1);
    }
#endif

    DPRINTLN(F("BlueMaus"));
    DPRINTLN(F("ohai"));

    // Initialize motor control pins
    pinMode(PIN_AIN1, OUTPUT);
    pinMode(PIN_AIN2, OUTPUT);
    pinMode(PIN_BIN1, OUTPUT);
    pinMode(PIN_BIN2, OUTPUT);
    pinMode(PIN_SLEEP, OUTPUT);
    pinMode(PIN_FAULT, INPUT_PULLUP);
    digitalWrite(PIN_AIN1, LOW);
    digitalWrite(PIN_AIN2, LOW);
    digitalWrite(PIN_BIN1, LOW);
    digitalWrite(PIN_BIN2, LOW);
    digitalWrite(PIN_SLEEP, LOW);

    // das blinkenlights off until connect
    Bluefruit.autoConnLed(true);

    // Config with max bandwidth (at the expense of SoftDevice SRAM)
    Bluefruit.configPrphBandwidth(BANDWIDTH_MAX);

    // NB: All configXXX() functions should be called before here!!
    Bluefruit.begin();
    DPRINTLN(F("Bluefruit: begun"));

    // More basic setup stuff
    Bluefruit.setTxPower(4); // magic?!?!
    Bluefruit.setName(BLE_UART_NAME);
    Bluefruit.Periph.setConnectCallback(connect_callback);
    Bluefruit.Periph.setDisconnectCallback(disconnect_callback);
    DPRINTLN(F("Bluefruit: callbacks set"));

    // Make sure to execute any incoming OTA DFUs
    ble_dfu.begin();
    DPRINTLN(F("Bluefruit: DFU (maybe) done"));

    // Setup DIS
    ble_dis.setManufacturer("Your Mama");
    ble_dis.setModel("BleuMaus v1.0");
    ble_dis.begin();
    DPRINTLN(F("Bluefruit: DIS online"));

    // Setup & start UART service
    ble_uart.begin();
    DPRINTLN(F("Bluefruit: UART started"));

    // Start BLE battery service
    ble_bas.begin();
    ble_bas.write(100);
    DPRINTLN(F("Bluefruit: Battery service started"));
    
    // Setup advertising packet
    Bluefruit.Advertising.addFlags(BLE_GAP_ADV_FLAGS_LE_ONLY_GENERAL_DISC_MODE);
    Bluefruit.Advertising.addTxPower();
    Bluefruit.Advertising.addService(ble_uart);

    // Name is only sent after discovery because BLE lol
    Bluefruit.ScanResponse.addName();

    // Start advertizing
    Bluefruit.Advertising.restartOnDisconnect(true);
    Bluefruit.Advertising.setInterval(32, 244); // in units of 0.625ms
    Bluefruit.Advertising.setFastTimeout(30); // number of seconds in fast mode
    Bluefruit.Advertising.start(0); // never stop advertising

    // Finally
    DPRINTLN(F("setup() done"));

}

void loop() {

    //
    // Command structure
    //
    // In lieu of a more complicated protocol, I've moved to an ASCII-based one
    // that uses the .parseInt() functions available to decendents of the
    // Stream class. The mouse looks for commands that look like this:
    //
    // L<integer>R<integer>
    //
    // Where "<integer>" is a ASCII-representatin decimal integer from 0 to
    // 255, i.e., used straight as input to analogWrite().
    //
  
    // If a command is available, read it, verify the checksum and then
    // dispatch if it passes.
    if (ble_uart.available()) {
        if (ble_uart.find("L")) {
            curr_motor_l = (int16_t) ble_uart.parseInt(SKIP_NONE);
            if (ble_uart.find("R")) {
                curr_motor_r = (int16_t) ble_uart.parseInt(SKIP_NONE);
                ble_uart.println("OK");
            } else {
                curr_motor_l = curr_motor_r = 0;
                ble_uart.println("WAT");
            }
        } else {
            curr_motor_l = curr_motor_r = 0;
            ble_uart.println("WAT");
        }
    }

    // If we are supposed to be moving, do so.
    dispatch_movement();

    // If timer has expired and we've been moving, stop.
    if (cmd_timer.hasPassed(CMD_DURATION)) {
        if (curr_motor_l != 0 || curr_motor_r != 0) {
            curr_motor_l = 0;
            curr_motor_r = 0;
        }
    }

    // Yield to do other stuff.
    delay(10);

}

// vi: syntax=arduino ts=4 sw=4

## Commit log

2017-11-23 first stabs at some hardware; initial ir and bt firmwares
2017-11-23 remove wdt crap
2017-11-23 now working UART thanks to jferretti
2017-11-28 bluefruit controller i can't use b/c needs to be a BT controller grr
2017-11-28 IR controlled two wheeled maus
2017-12-05 attempt to make an attiny85 version
2017-12-05 various attempts at an attiny85 based board:
2017-12-05 initial commit of redbear ble nano2.0 daughter board
2017-12-14 working (\!) IR diff drive
2017-12-14 initial rev of ble nano2 daughter board
2017-12-21 fatmouse works!
2017-12-25 more futzing around with BLE board design
2017-12-25 some notes on the hexbug IR remote RE i attempted
2018-01-06 lkvfjkladsjf
2018-01-06 lkasdjfaldsj
2018-01-13 moar boards
2018-01-13 removing duplicate, mis-versioned copy
2018-01-13 simple test to try to find the range of the joystick
2018-01-13 let's try this with irlib2
2018-01-14 more testing code
2018-01-17 testing sending
2018-01-19 and finally working wii nunchuk version
2018-01-19 more polish and low power usage for coil cell operation
2018-01-19 added CRC16 checks to remote output
2018-01-19 should have branched this but oh well
2019-08-23 various new hw design revisions
2019-08-23 ignore some stuff
2019-08-23 using another feather for a remote control
2019-08-24 progress
2019-09-01 further work
2019-09-04 more tweaking
2019-09-04 more futzing
2019-09-06 protocol structure changed to ASCII
2019-09-06 matching client changes
2019-09-25 cleanup
2019-09-25 works on the prototype but not the new board sigh

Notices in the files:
parts and their libraries:
a_parts: Released under the Creative Commons Attribution Share-Alike 4.0 License
a_parts: https://creativecommons.org/licenses/by-sa/4.0
a_parts: Released under the Creative Commons
